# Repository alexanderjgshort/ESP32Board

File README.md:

# ESP32Board

Generic prototyping board done in KiCad 7.0 using the ESP32-Wrover module.

Here is a screenshot of the finished board in the 3D Viewer

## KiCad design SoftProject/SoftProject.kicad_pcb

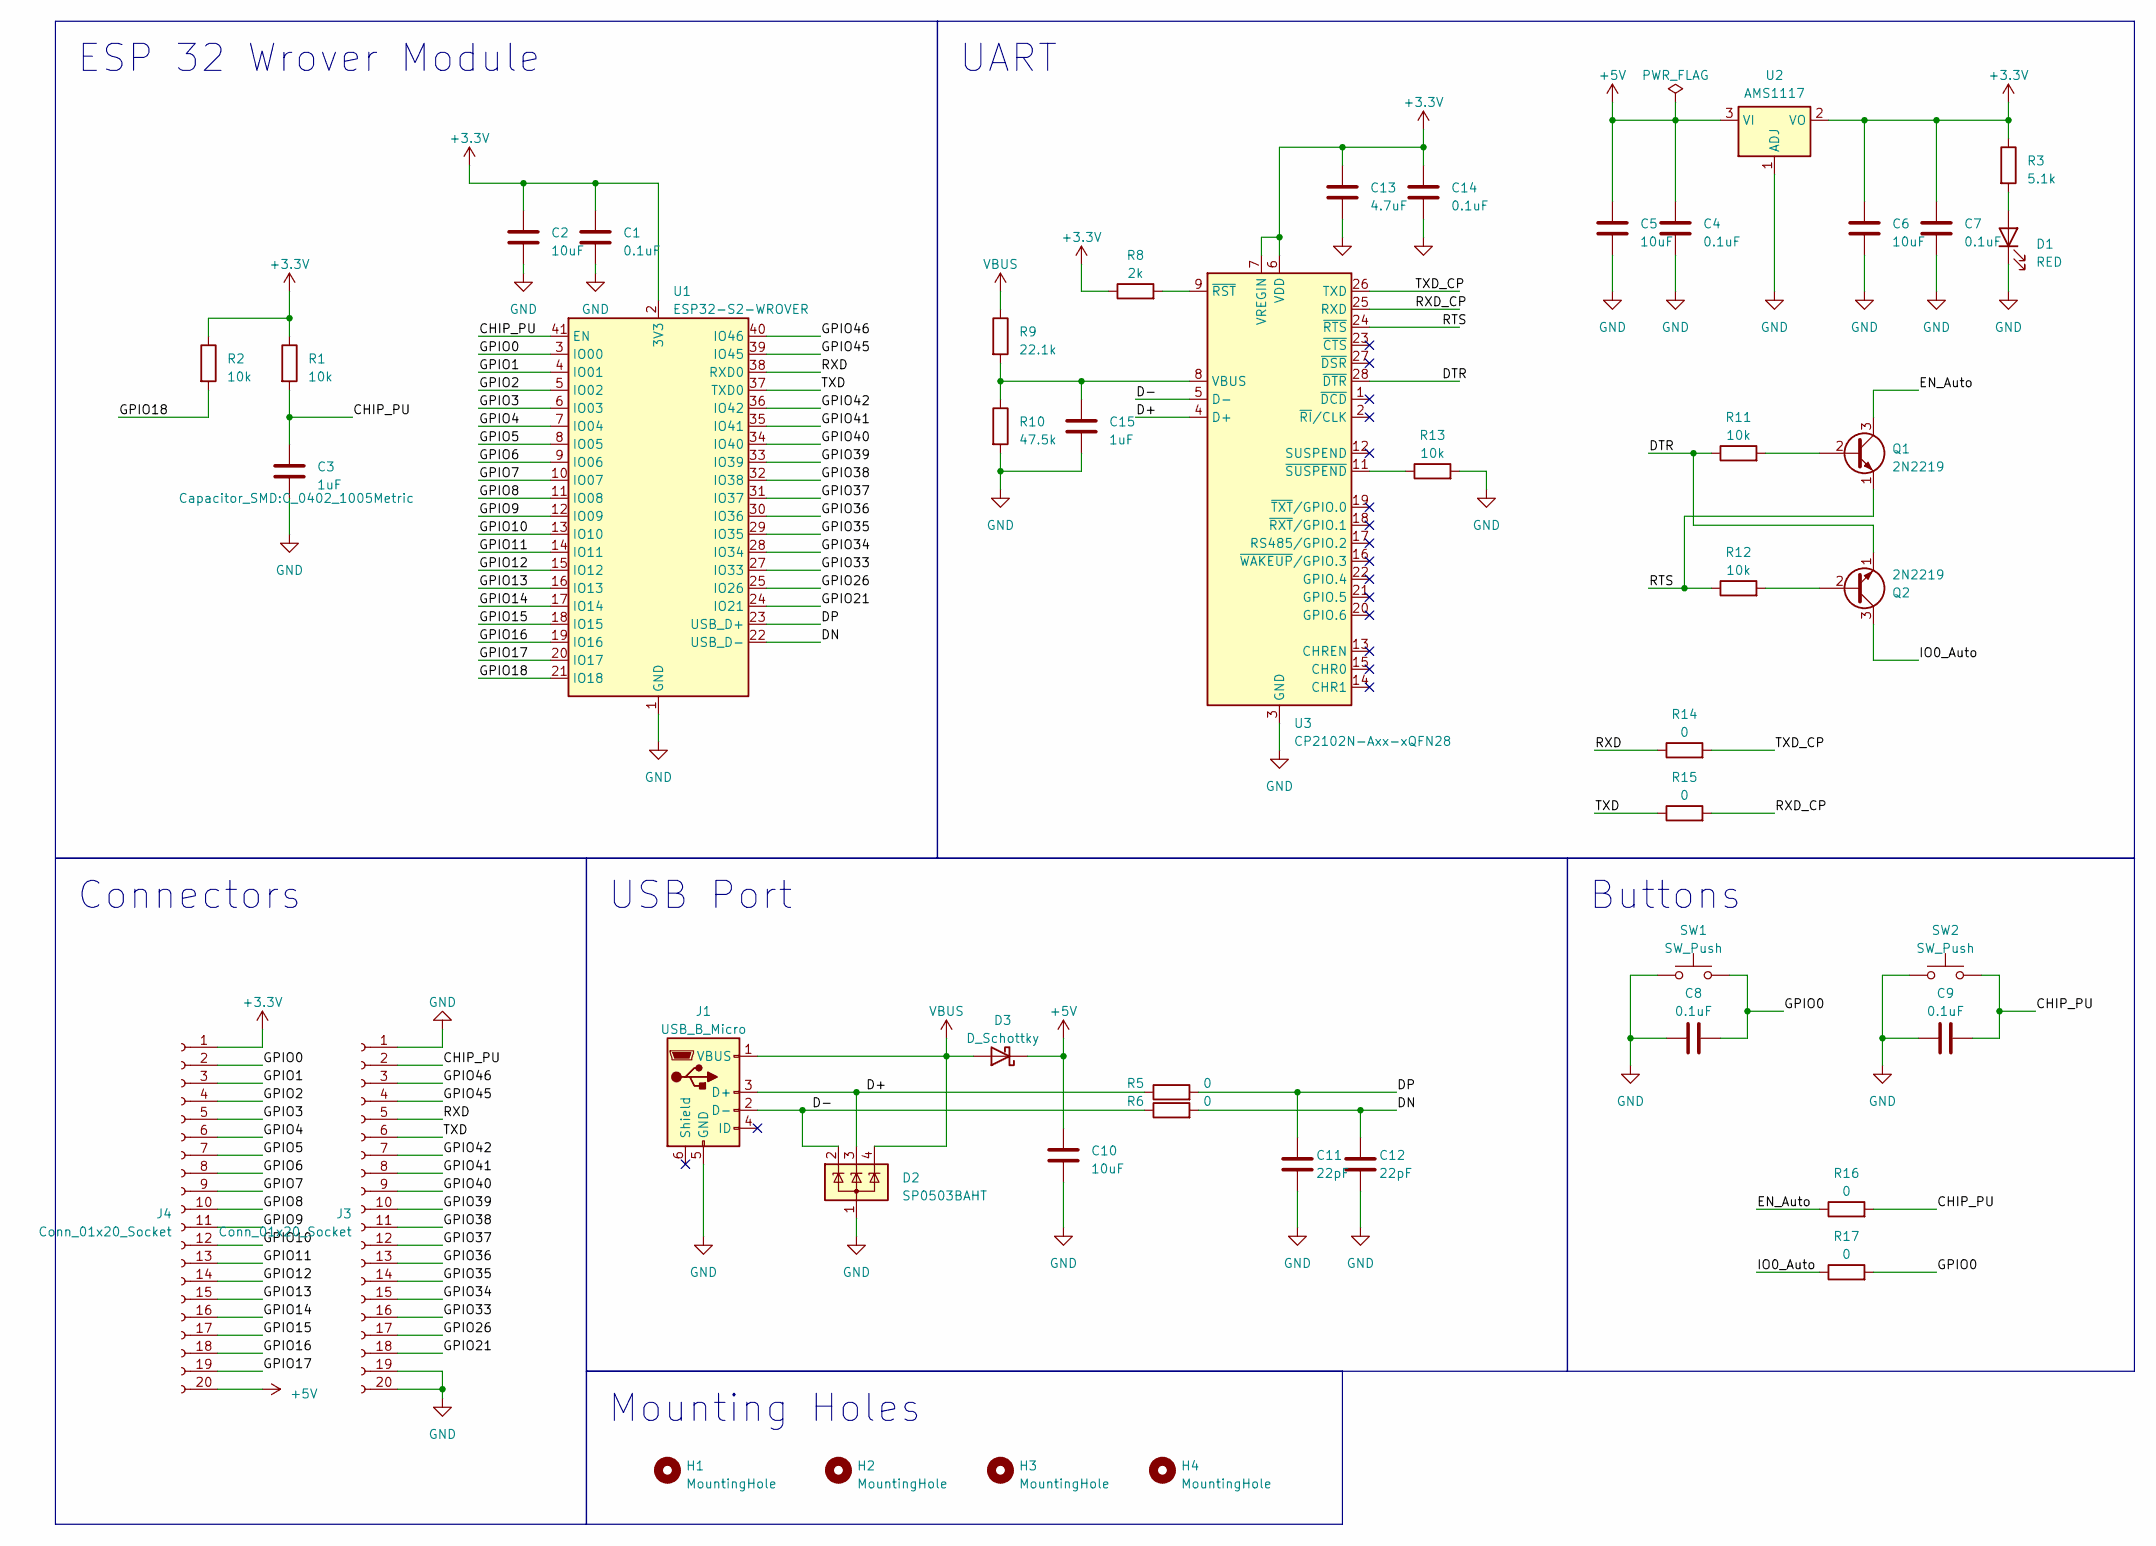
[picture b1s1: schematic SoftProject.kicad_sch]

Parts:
C1, C4, C7, C8, C9, C14: 0.1uF; C_0402_1005Metric; JLCPCB Part Number C105883
C2, C5, C6, C10: 10uF; C_0805_2012Metric; JLCPCB Part Number C440198
C3, C15: 1uF; C_0402_1005Metric; JLCPCB Part Number C326568
C11, C12: 22pF; C_0402_1005Metric; JLCPCB Part Number C147430
C13: 4.7uF; C_0603_1608Metric; JLCPCB Part Number C2171286
D1: RED; LED_0603_1608Metric; JLCPCB Part Number C84263
D2: SP0503BAHT; SOT-143; JLCPCB Part Number C3040626
D3: D_Schottky; D_SOD-323; JLCPCB Part Number C116158
H1, H2, H3, H4: MountingHole; MountingHole_2.2mm_M2
J1: USB_B_Micro; USB_Micro-B_Molex-105017-0001; JLCPCB Part Number C136000
J3, J4: Conn_01x20_Socket; PinSocket_1x20_P2.54mm_Vertical
Q1, Q2: 2N2219; SOT-23; JLCPCB Part Number C475630
R1, R2, R11, R12, R13: 10k; R_0402_1005Metric; JLCPCB Part Number C409612
R3: 5.1k; R_0402_1005Metric; JLCPCB Part Number C147799
R5, R6, R14, R15, R16, R17: 0; R_0402_1005Metric; JLCPCB Part Number C279984
R8: 2k; R_0402_1005Metric; JLCPCB Part Number C409711
R9: 22.1k; R_0402_1005Metric; JLCPCB Part Number C325588
R10: 47.5k; R_0402_1005Metric; JLCPCB Part Number C319604
SW1, SW2: SW_Push; B3U-1000P; JLCPCB Part Number C231329
U1: ESP32-S2-WROVER; JLCPCB Part Number C701333
U2: AMS1117; SOT-223-3_TabPin2; JLCPCB Part Number C369933
U3: CP2102N-Axx-xQFN28; QFN-28-1EP_5x5mm_P0.5mm_EP3.35x3.35mm; JLCPCB Part Number C964632

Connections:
+3.3V: C1.1, C2.1, C6.1, C7.1, C13.1, C14.1, J4.1, R1.1, R2.1, R3.1, R8.1, U1.2 (3V3), U2.2 (VO), U3.6 (VDD), U3.7 (VREGIN)
+5V: C4.1, C5.1, C10.1, D3.1 (K), J4.20, U2.3 (VI)
/CHIP_PU: C3.1, C9.2, J3.2, R1.2, R16.2, SW2.2, U1.41 (EN)
/D+: D2.3 (K), J1.3 (D+), R5.1, U3.4 (D+)
/D-: D2.2 (K), J1.2 (D-), R6.1, U3.5 (D-)
/DN: C12.1, R6.2, U1.22 (USB_D-)
/DP: C11.1, R5.2, U1.23 (USB_D+)
/DTR: Q2.1 (E), R11.1, U3.28 (~DTR)
/EN_Auto: Q1.3 (C), R16.1
/GPIO0: C8.2, J4.2, R17.2, SW1.2, U1.3 (IO00)
/GPIO1: J4.3, U1.4 (IO01)
/GPIO2: J4.4, U1.5 (IO02)
/GPIO3: J4.5, U1.6 (IO03)
/GPIO4: J4.6, U1.7 (IO04)
/GPIO5: J4.7, U1.8 (IO05)
/GPIO6: J4.8, U1.9 (IO06)
/GPIO7: J4.9, U1.10 (IO07)
/GPIO8: J4.10, U1.11 (IO08)
/GPIO9: J4.11, U1.12 (IO09)
/GPIO10: J4.12, U1.13 (IO10)
/GPIO11: J4.13, U1.14 (IO11)
/GPIO12: J4.14, U1.15 (IO12)
/GPIO13: J4.15, U1.16 (IO13)
/GPIO14: J4.16, U1.17 (IO14)
/GPIO15: J4.17, U1.18 (IO15)
/GPIO16: J4.18, U1.19 (IO16)
/GPIO17: J4.19, U1.20 (IO17)
/GPIO18: R2.2, U1.21 (IO18)
/GPIO21: J3.18, U1.24 (IO21)
/GPIO26: J3.17, U1.25 (IO26)
/GPIO33: J3.16, U1.27 (IO33)
/GPIO34: J3.15, U1.28 (IO34)
/GPIO35: J3.14, U1.29 (IO35)
/GPIO36: J3.13, U1.30 (IO36)
/GPIO37: J3.12, U1.31 (IO37)
/GPIO38: J3.11, U1.32 (IO38)
/GPIO39: J3.10, U1.33 (IO39)
/GPIO40: J3.9, U1.34 (IO40)
/GPIO41: J3.8, U1.35 (IO41)
/GPIO42: J3.7, U1.36 (IO42)
/GPIO45: J3.4, U1.39 (IO45)
/GPIO46: J3.3, U1.40 (IO46)
/IO0_Auto: Q2.3 (C), R17.1
/RTS: Q1.1 (E), R12.1, U3.24 (~RTS)
/RXD: J3.5, R14.1, U1.38 (RXD0)
/RXD_CP: R15.2, U3.25 (RXD)
/TXD: J3.6, R15.1, U1.37 (TXD0)
/TXD_CP: R14.2, U3.26 (TXD)
GND: C1.2, C2.2, C3.2, C4.2, C5.2, C6.2, C7.2, C8.1, C9.1, C10.2, C11.2, C12.2, C13.2, C14.2, C15.2, D1.1 (K), D2.1 (A), J1.5 (GND), J3.1, J3.19, J3.20, R10.2, R13.2, SW1.1, SW2.1, U1.1 (GND), U1.26 (GND), U1.42 (GND), U1.43 (GND), U2.1 (ADJ), U3.3 (GND), U3.29 (GND)
unnamed: D1.2 (A), R3.2
unnamed: Q1.2 (B), R11.2
unnamed: Q2.2 (B), R12.2
unnamed: C15.1, R9.2, R10.1, U3.8 (VBUS)
unnamed: R8.2, U3.9 (~RST)
unnamed: R13.1, U3.11 (~SUSPEND)
VBUS: D2.4 (K), D3.2 (A), J1.1 (VBUS), R9.1

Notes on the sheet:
Buttons
Mounting Holes
UART
ESP 32 Wrover Module
USB Port
Connectors

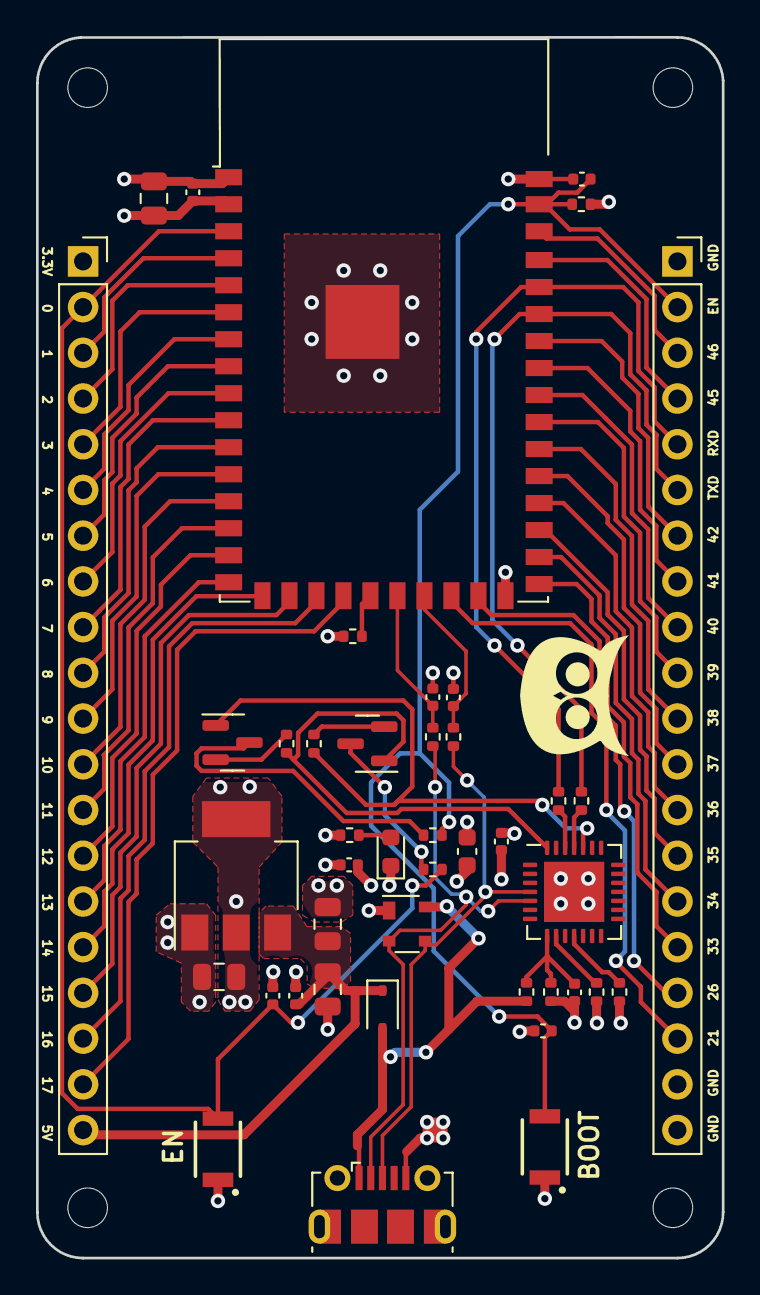
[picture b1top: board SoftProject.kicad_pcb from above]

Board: 4 copper layers, 38.1 x 67.8 mm, 47 parts (0 on the bottom side), 56 nets.

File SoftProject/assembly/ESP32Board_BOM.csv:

Comment,Reference,Footprint,JLCPCB Part #
0.1uF,"C1, C4, C7, C8, C9, C14",Capacitor_SMD:C_0402_1005Metric,C105883
10uF,"C2, C5, C6, C10",Capacitor_SMD:C_0805_2012Metric,C440198
1uF,"C3, C15",Capacitor_SMD:C_0402_1005Metric,C326568
22pF,"C11, C12",Capacitor_SMD:C_0402_1005Metric,C147430
4.7uF,C13,Capacitor_SMD:C_0603_1608Metric,C2171286
RED,D1,LED_SMD:LED_0603_1608Metric,C84263
SP0503BAHT,D2,Package_TO_SOT_SMD:SOT-143,C3040626
D_Schottky,D3,Diode_SMD:D_SOD-323,C116158
MountingHole,"H1, H2, H3, H4",MountingHole:MountingHole_2.2mm_M2,
USB_B_Micro,J1,Connector_USB:USB_Micro-B_Molex-105017-0001,C136000
Conn_01x20_Socket,"J3, J4",Connector_PinSocket_2.54mm:PinSocket_1x20_P2.54mm_Vertical,
2N2219,"Q1, Q2",Package_TO_SOT_SMD:SOT-23,C475630
10k,"R1, R2, R11, R12, R13",Resistor_SMD:R_0402_1005Metric,C409612
5.1k,R3,Resistor_SMD:R_0402_1005Metric,C147799
0,"R5, R6, R14, R15, R16, R17",Resistor_SMD:R_0402_1005Metric,C279984
2k,R8,Resistor_SMD:R_0402_1005Metric,C409711
22.1k,R9,Resistor_SMD:R_0402_1005Metric,C325588
47.5k,R10,Resistor_SMD:R_0402_1005Metric,C319604
SW_Push,"SW1, SW2",B3U-1000P:B3U-1000P,C231329
ESP32-S2-WROVER,U1,RF_Module:ESP32-S2-WROVER,C701333
AMS1117,U2,Package_TO_SOT_SMD:SOT-223-3_TabPin2,C369933
CP2102N-Axx-xQFN28,U3,Package_DFN_QFN:QFN-28-1EP_5x5mm_P0.5mm_EP3.35x3.35mm,C964632

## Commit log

2023-05-19 Started schematic of ESP32 board
2023-05-24 Finished schematic
2023-05-26 Added some footprints
2023-06-02 Finished layout. Started routing.
2023-06-04 Finished layout and routing
2023-06-11 Finished ESP32Board
2023-06-13 Finished and ordered PCB
